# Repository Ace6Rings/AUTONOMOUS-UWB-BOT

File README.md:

# AUTONOMOUS-UWB-BOT
A ground robot with four UWB anchors to determine its location via TDoA or ToF.

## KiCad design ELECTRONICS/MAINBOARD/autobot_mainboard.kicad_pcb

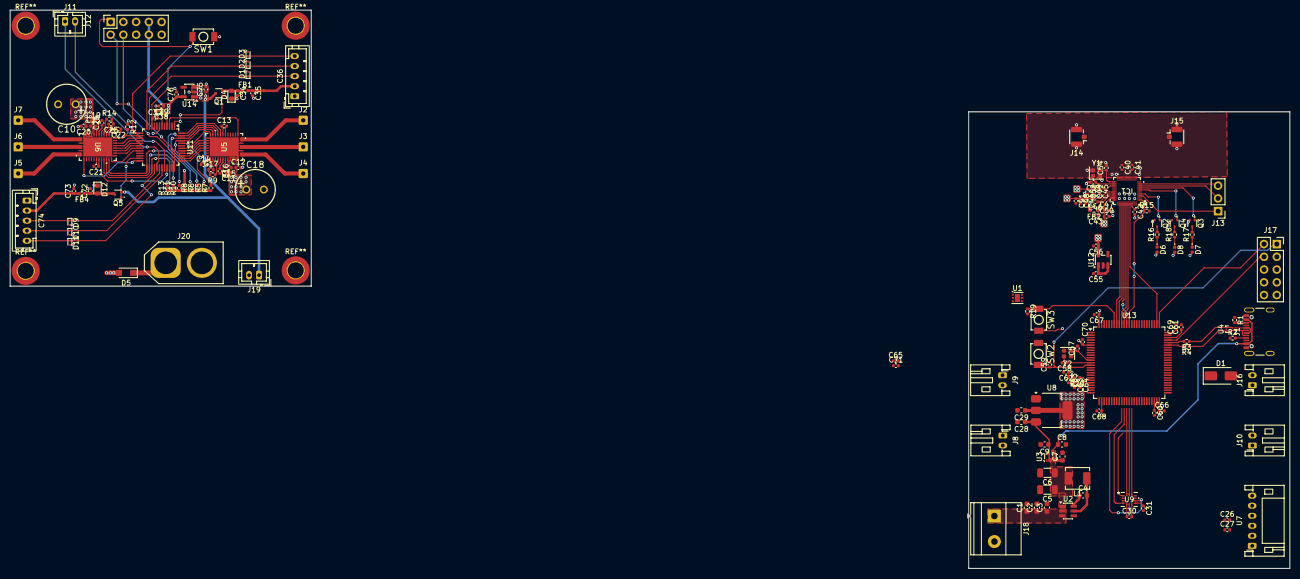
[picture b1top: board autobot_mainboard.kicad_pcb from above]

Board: 4 copper layers, 255.0 x 111.2 mm, 156 parts (0 on the bottom side), 122 nets.

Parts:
C1, C28, C29: 10u; C_0603_1608Metric
C2: 1u; C_0603_1608Metric
C3, C4, C7, C8: 100n; C_0603_1608Metric
C5, C6: 22u; C_1206_3216Metric
C9: 4u7; C_0603_1608Metric
C10, C18: 100u; CAP-TH_BD8.0-P3.50-D0.6-FD
C11, C12, C19, C20, C26, C30, C31, C37, C38, C42, C47, C48, C49, C59, C62, C64, C65, C66, C67, C68, C69, C70: 100n; C_0402_1005Metric
C13, C14, C15, C21, C22, C23, C55, C56, C63, C75, C76: 1u; C_0402_1005Metric
C16, C24: 47n; C_0402_1005Metric
C17, C25, C34, C35, C72, C73: C; C_0402_1005Metric
C27, C51, C52: 10u; C_0402_1005Metric
C36, C74: AMT-102-V; JST_PH_B5B-PH-K_1x05_P2.00mm_Vertical
C39, C71: 4u7; C_0402_1005Metric
C40, C41: 2p; C_0402_1005Metric
C43, C44, C45: 4.7n; C_0402_1005Metric
C46: 220n; C_0402_1005Metric
C50: 4.7u; C_0402_1005Metric
C53, C54, C57, C58: 12p; C_0402_1005Metric
C60, C61: 2.2u; C_0402_1005Metric
D1, D2, D3, D9, D10, D11: D_TVS; D_SOD-923
D1#2: SS24; D_SMA
D4, D12: D_TVS; D_0603_1608Metric
D5: PTVS17VZ1USK; Nexperia_CFP3_SOD-123W
D6, D7, D8: LED; LED_0402_1005Metric
FB1, FB3, FB4: FerriteBead_Small; R_0402_1005Metric
FB2: fb; R_0603_1608Metric
IC1: DW3210; qfn_DW3220_QOR-M
J1: USB_C_Receptacle_USB2.0_16P; USB_C_Receptacle_GCT_USB4105-xx-A_16P_TopMnt_Horizontal
J2, J3, J4, J5, J6, J7: Conn_01x01_Socket; SolderWire-0.25sqmm_1x01_D0.65mm_OD1.7mm
J8, J9, J10, J16: Conn_01x02_Pin; JST_PH_S2B-PH-K_1x02_P2.00mm_Horizontal
J11: Conn_01x02_Socket; JST_PH_B2B-PH-K_1x02_P2.00mm_Vertical
J12, J17: Conn_02x05_Odd_Even; PinSocket_2x05_P2.54mm_Vertical
J13: Conn_01x03_Pin; PinHeader_1x03_P2.54mm_Vertical
J14, J15: Conn_Coaxial; U.FL_Hirose_U.FL-R-SMT-1_Vertical
J18: Conn_01x02_Pin; TerminalBlock_Phoenix_MKDS-1,5-2-5.08_1x02_P5.08mm_Horizont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
J19: Conn_01x02_Pin; JST_PH_B2B-PH-K_1x02_P2.00mm_Vertical
J20: Conn_01x02_Pin; AMASS_XT60-F_1x02_P7.20mm_Vertical
L1: 4u7; L_Chilisin_BMRA00040415
Q1, Q2, Q3, Q4, Q5: DMG1012T; SOT-523
R1, R2: 5.1k; R_0402_1005Metric
R3, R4, R9, R14: 22; R_0402_1005Metric
R5, R6, R7, R8, R10, R11, R12, R13: 10K; R_0402_1005Metric
R15: 100K; R_0402_1005Metric
R16, R17, R18: R; R_0402_1005Metric
R19: 10k; R_0402_1005Metric
R20: 47; R_0402_1005Metric_Pad0.72x0.64mm_HandSolder
SW1: SW_Push; SW-SMD_L3.9-W3.0-P4.45
SW2: RESET; SW-SMD_L3.9-W3.0-P4.45
SW3: BOOT; SW-SMD_L3.9-W3.0-P4.45
U1: TVS1400DRV; WSON-6-1EP_2x2mm_P0.65mm_EP1x1.6mm
U2: AP63205WU; TSOT-23-6
U3: TPS2116DRL; SOT-583-8
U4: TPD2EUSB30A; Texas_DRT-3
U5, U6: VQFN40_RGF_TEX_mct8316
U7: VL53L1X; JST_PH_S6B-PH-K_1x06_P2.00mm_Horizontal
U8: NCP1117-3.3_SOT223; SOT-223-3_TabPin2
U9: BMI270; BMI270_BOS-M
U11: STM32G031C_4-6-8_Tx; LQFP-48_7x7mm_P0.5mm
U12, U14: LP5907MFX-3.3; SOT-23-5
U13: STM32H743VITx; LQFP-100_14x14mm_P0.5mm
Y1: TXC 8Y38472012; Crystal_SMD_2016-4Pin_2.0x1.6mm
Y2: 25mhz placeholder; Crystal_SMD_2016-4Pin_2.0x1.6mm

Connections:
+3V3: C26.1, C27.1, C29.1, C38.1, C39.1, C44.1, C45.1, C47.1, C48.1, C49.1, C50.1, C51.1, C52.1, C56.1, C62.1, C65.1, C66.1, C67.1, C68.1, C69.1, C70.1, C71.1, C76.1, D6.2 (A), D7.2 (A), D8.2 (A), FB2.2, FB3.1, IC1.23 (VDD2B), IC1.26 (VDD3), IC1.29 (VDD1), J12.7, J12.8, J17.7, J17.8, R5.1, R6.1, R7.1, R8.1, R10.1, R11.1, R12.1, R13.1, SW3.2, U7.1 (VIN), U8.2 (VO), U11.4 (VBAT), U11.6 (VDD), U12.5 (OUT), U13.6 (VBAT), U13.11 (VDD), U13.27 (VDD), U13.50 (VDD), U13.75 (VDD), U13.100 (VDD), U14.5 (OUT)
+5V: C9.1, C28.1, C30.1, C31.1, C34.1, C55.1, C72.1, C75.1, D4.2 (A2), D12.2 (A2), FB1.1, FB4.1, J19.1, Q1.2 (S), Q1.3 (D), Q5.2 (S), Q5.3 (D), U3.2 (VOUT), U3.7 (VOUT), U8.3 (VI), U9.5 (VDDIO), U9.8 (VDD), U12.1 (IN), U12.3 (EN), U14.1 (IN), U14.3 (EN)
+24V: C10.1, C11.1, C12.1, C15.1, C18.1, C19.1, C20.1, C23.1, D5.1 (K), J20.1, U5.9 (VM), U5.10 (VM), U5.11 (VM), U6.9 (VM), U6.10 (VM), U6.11 (VM)
/AMT102_L/AMT_A: C36.3 (A), D1.1 (A1), U11.11 (PA0)
/AMT102_L/AMT_B: C36.4 (B), D2.1 (A1), U11.12 (PA1)
/AMT102_L/AMT_GATE: Q1.1 (G), U11.1 (PC13)
/AMT102_L/AMT_X: C36.5 (X), D3.1 (A1), U11.13 (PA2)
/AMT102_R/AMT_A: C74.3 (A), D9.1 (A1), U11.30 (PC6)
/AMT102_R/AMT_B: C74.4 (B), D10.1 (A1), U11.31 (PC7)
/AMT102_R/AMT_GATE: Q5.1 (G), U11.23 (PB11)
/AMT102_R/AMT_X: C74.5 (X), D11.1 (A1), U11.28 (PA8)
/BMI270_L/BMI_CS: U9.12 (CSB), U13.41 (PE11)
/BMI270_L/BMI_MISO: U9.1 (SDO), U13.43 (PE13)
/BMI270_L/BMI_MOSI: U9.14 (SDX), U13.44 (PE14)
/BMI270_L/BMI_SCK: U9.13 (SCX), U13.42 (PE12)
/DW3220_T/CSN: IC1.37 (SPICSN), U13.77 (PA15)
/DW3220_T/DW_GPIO0: IC1.3 (GPIO0/_RXOKLED), J13.1
/DW3220_T/DW_GPIO4: IC1.8 (GPIO4/_EXTPA), J13.2
/DW3220_T/DW_GPIO7: IC1.9 (GPIO7/_SYNC), J13.3
/DW3220_T/DW_RF1: C40.1, J14.1 (In)
/DW3220_T/DW_RF2: C41.1, J15.1 (In)
/DW3220_T/IRQ: IC1.1 (IRQ/_GPIO8), R15.1, U13.88 (PD7)
/DW3220_T/MISO: IC1.36 (SPICDO_(SPIMISO)), U13.90 (PB4)
/DW3220_T/MOSI: IC1.35 (SPICDI_(SPIMOSI)), U13.91 (PB5)
/DW3220_T/RESET: IC1.33 (RSTN), U13.92 (PB6)
/DW3220_T/RXLED: IC1.6 (GPIO2_/_RXLED), Q4.1 (G)
/DW3220_T/RX_OK_LED: IC1.4 (GPIO1/_SFDLED), Q2.1 (G)
/DW3220_T/SPICLK: IC1.34 (SPICLK), U13.89 (PB3)
/DW3220_T/TXLED: IC1.7 (GPIO3_/_TXLED), Q3.1 (G)
/DW3220_T/WAKEUP: IC1.32 (WAKEUP), U13.93 (PB7)
/DW3220_T/XTI: C54.1, IC1.21 (XTI), Y1.3
/DW3220_T/XTO: C53.1, IC1.22 (XTO), Y1.1
/POWER_CONNECTOR/12V: C1.1, C2.1, C3.1, J18.1, U1.4 (IN), U1.5 (IN), U1.6 (IN), U2.2 (EN), U2.3 (IN)
/POWER_MAINBOARD/BUCK_5V: C5.1, C6.1, C7.1, L1.2, U2.1 (FB), U3.3 (VIN1), U3.4 (PR1), U3.5 (MODE)
/POWER_MAINBOARD/VBUS: C8.1, J1.A4 (VBUS), J1.A9 (VBUS), J1.B4 (VBUS), J1.B9 (VBUS), U3.6 (VIN2)
/STM32G0/BRAKE: U5.35 (BRAKE), U11.40 (PD2)
/STM32G0/BRAKE_R: U6.35 (BRAKE), U11.18 (PA7)
/STM32G0/DACOUT1: U5.37 (DACOUT1), U11.38 (PD0)
/STM32G0/DACOUT1_R: U6.37 (DACOUT1), U11.16 (PA5)
/STM32G0/DACOUT2: U5.38 (DACOUT2), U11.37 (PA15)
/STM32G0/DACOUT2_R: U6.38 (DACOUT2), U11.15 (PA4)
/STM32G0/DACOUT2/SOX: U5.36 (DACOUT2/SOX), U11.39 (PD1)
/STM32G0/DACOUT2/SOX_R: U6.36 (DACOUT2/SOX), U11.17 (PA6)
/STM32G0/DIR: U5.34 (DIR), U11.41 (PD3)
/STM32G0/DIR_R: U6.34 (DIR), U11.19 (PB0)
/STM32G0/DRVOFF: U5.21 (DRVOFF), U11.3 (PC15)
/STM32G0/DRVOFF_R: U6.21 (DRVOFF), U11.24 (PB12)
/STM32G0/EXT_WD: U5.32 (EXT_WD), U11.42 (PB3)
/STM32G0/EXT_WD_R: U6.32 (EXT_WD), U11.20 (PB1)
/STM32G0/FG: R8.2, U5.29 (FG), U11.47 (PB8)
/STM32G0/FG_R: R13.2, U6.29 (FG), U11.27 (PB15)
/STM32G0/PWM: U5.28 (SPEED/WAKE), U11.48 (PB9)
/STM32G0/PWM_R: U6.28 (SPEED/WAKE), U11.33 (PA9/PA11)
/STM32G0/SCL: R5.2, U5.31 (SCL), U11.45 (PB6)
/STM32G0/SCL_R: R10.2, U6.31 (SCL), U11.25 (PB13)
/STM32G0/SDA: R6.2, U5.30 (SDA), U11.46 (PB7)
/STM32G0/SDA_R: R11.2, U6.30 (SDA), U11.26 (PB14)
/STM32G0/SWCLK: J12.2, U11.36 (PA14)
/STM32G0/SWDIO: J12.4, U11.35 (PA13)
/STM32G0/USART_RX: J11.2, J16.1, U11.32 (NC/PA10), U13.53 (PB14)
/STM32G0/USART_TX: J11.1, J16.2, U11.29 (NC/PA9), U13.54 (PB15)
/STM32G0/nFAULT: R7.2, U5.40 (nFAULT), U11.44 (PB5)
/STM32G0/nFAULT_R: R12.2, U6.40 (nFAULT), U11.14 (PA3)
/STM32G0/nRESET: C37.1, J12.1, SW1.2, U11.10 (PF2)
/STM32H743/BOOT0: R19.1, SW3.1, U13.94 (BOOT0)
/STM32H743/D+: R3.2, U13.71 (PA12)
/STM32H743/D-: R4.2, U13.70 (PA11)
/STM32H743/NRST: C59.1, J17.1, SW2.2, U13.14 (NRST)
/STM32H743/PH0: C57.1, U13.12 (PH0), Y2.1
/STM32H743/PH1: C58.1, U13.13 (PH1), Y2.3
/STM32H743/SWCLK: J17.2, U13.76 (PA14)
/STM32H743/SWDIO: J17.4, U13.72 (PA13)
/STM32H743/VREF: R20.1, U13.20 (VREF+)
/USB/DATA +: J1.A6 (D+), J1.B6 (D+), R3.1, U4.2 (D-)
/USB/DATA -: J1.A7 (D-), J1.B7 (D-), R4.1, U4.1 (D+)
GNDREF: C1.2, C2.2, C3.2, C5.2, C6.2, C7.2, C8.2, C9.2, C10.2, C11.2, C12.2, C18.2, C19.2, C20.2, C26.2, C27.2, C28.2, C29.2, C30.2, C31.2, C34.2, C35.2, C36.1 (GND), C37.2, C38.2, C39.2, C42.2, C43.2, C44.2, C45.2, C46.2, C47.2, C48.2, C49.2, C50.2, C51.2, C52.2, C53.2, C54.2, C55.2, C56.2, C57.2, C58.2, C59.2, C60.2, C61.2, C62.2, C63.2, C64.2, C65.2, C66.2, C67.2, C68.2, C69.2, C70.2, C71.2, C72.2, C73.2, C74.1 (GND), C75.2, C76.2, D1.2 (A2), D2.2 (A2), D3.2 (A2), D4.1 (A1), D5.2 (A), D9.2 (A2), D10.2 (A2), D11.2 (A2), D12.1 (A1), IC1.2 (GPIO6_/_EXTRXE_/_SPIPHA), IC1.5 (GPIO5_/_EXTTXE_/_SPIPOL), IC1.10 (GND_1), IC1.11 (GND_2), IC1.12 (GND_3), IC1.14 (GND_4), IC1.15 (GND_5), IC1.16 (GND_6), IC1.17 (GND_7), IC1.19 (GND_8), IC1.20 (GND_9), IC1.24 (VSS2), IC1.25 (VSS3), IC1.30 (VSS1), IC1.39 (VSS), IC1.40 (VSS), J1.A1 (GND), J1.A12 (GND), J1.B1 (GND), J1.B12 (GND), J1.SH (SHIELD), J12.5, J12.6, J14.2 (Ext), J15.2 (Ext), J17.5, J17.6, J18.2, J19.2, J20.2, Q2.2 (S), Q3.2 (S), Q4.2 (S), R1.1, R2.1, R15.2, R19.2, SW1.1, SW2.1, U1.1 (GND), U1.2 (GND), U1.3 (GND), U1.7 (GND), U2.4 (GND), U3.1 (GND), U4.3 (GND), U5.12 (PGND), U5.15 (PGND), U5.18 (PGND), U5.33 (EXT_CLK), U5.41 (GNDPAD), U6.12 (PGND), U6.15 (PGND), U6.18 (PGND), U6.33 (EXT_CLK), U6.41 (GNDPAD), U7.2 (GND), U8.1 (GND), U9.6 (GNDIO), U9.7 (GND), U11.7 (VSS), U12.2 (GND), U13.10 (VSS), U13.19 (VSSA), U13.26 (VSS), U13.49 (VSS), U13.74 (VSS), U13.99 (VSS), U14.2 (GND), Y1.2 (G), Y1.4 (G), Y2.2 (G), Y2.4 (G)
unnamed: C35.1, C36.2 (VIN), FB1.2
unnamed: C60.1, U13.48 (VCAP)
unnamed: C61.1, U13.73 (VCAP)
unnamed: C73.1, C74.2 (VIN), FB4.2
unnamed: D6.1 (K), R16.1
unnamed: D7.1 (K), R17.1
unnamed: D8.1 (K), R18.1
unnamed: C40.2, IC1.18 (RF1)
unnamed: C41.2, IC1.13 (RF2)
unnamed: C43.1, FB2.1, IC1.28 (VDD2A)
unnamed: C42.1, IC1.38 (VIO_D)
unnamed: C46.1, IC1.27 (VTX_D)
unnamed: J1.A5 (CC1), R2.2
unnamed: J1.B5 (CC2), R1.2
unnamed: J2.1 (Pin_1_1), U5.19 (OUTC), U5.20 (OUTC)
unnamed: J3.1 (Pin_1_1), U5.16 (OUTB), U5.17 (OUTB)
unnamed: J4.1 (Pin_1_1), U5.13 (OUTA), U5.14 (OUTA)
unnamed: J5.1 (Pin_1_1), U6.19 (OUTC), U6.20 (OUTC)
unnamed: J6.1 (Pin_1_1), U6.16 (OUTB), U6.17 (OUTB)
unnamed: J7.1 (Pin_1_1), U6.13 (OUTA), U6.14 (OUTA)
unnamed: Q2.3 (D), R16.2
unnamed: Q3.3 (D), R17.2
unnamed: Q4.3 (D), R18.2
unnamed: C4.1, U2.6 (BST)
unnamed: C4.2, L1.1, U2.5 (SW)
unnamed: C13.2, U5.26 (AGND)
unnamed: C13.1, U5.27 (AVDD)
unnamed: C15.2, U5.8 (CP)
unnamed: C16.2, U5.7 (CPH)
unnamed: C16.1, U5.6 (CPL)
unnamed: C14.2, U5.2 (DGND)
unnamed: C14.1, U5.1 (DVDD)
unnamed: C17.1, R9.2, U5.3 (FB_BK)
unnamed: C17.2, U5.4 (GND_BK)
unnamed: R9.1, U5.5 (SW_BK)
unnamed: C21.2, U6.26 (AGND)
unnamed: C21.1, U6.27 (AVDD)
unnamed: C23.2, U6.8 (CP)
unnamed: C24.2, U6.7 (CPH)
unnamed: C24.1, U6.6 (CPL)
unnamed: C22.2, U6.2 (DGND)
unnamed: C22.1, U6.1 (DVDD)
unnamed: C25.1, R14.2, U6.3 (FB_BK)
unnamed: C25.2, U6.4 (GND_BK)
unnamed: R14.1, U6.5 (SW_BK)
unnamed: C63.1, C64.1, FB3.2, R20.2, U13.21 (VDDA)

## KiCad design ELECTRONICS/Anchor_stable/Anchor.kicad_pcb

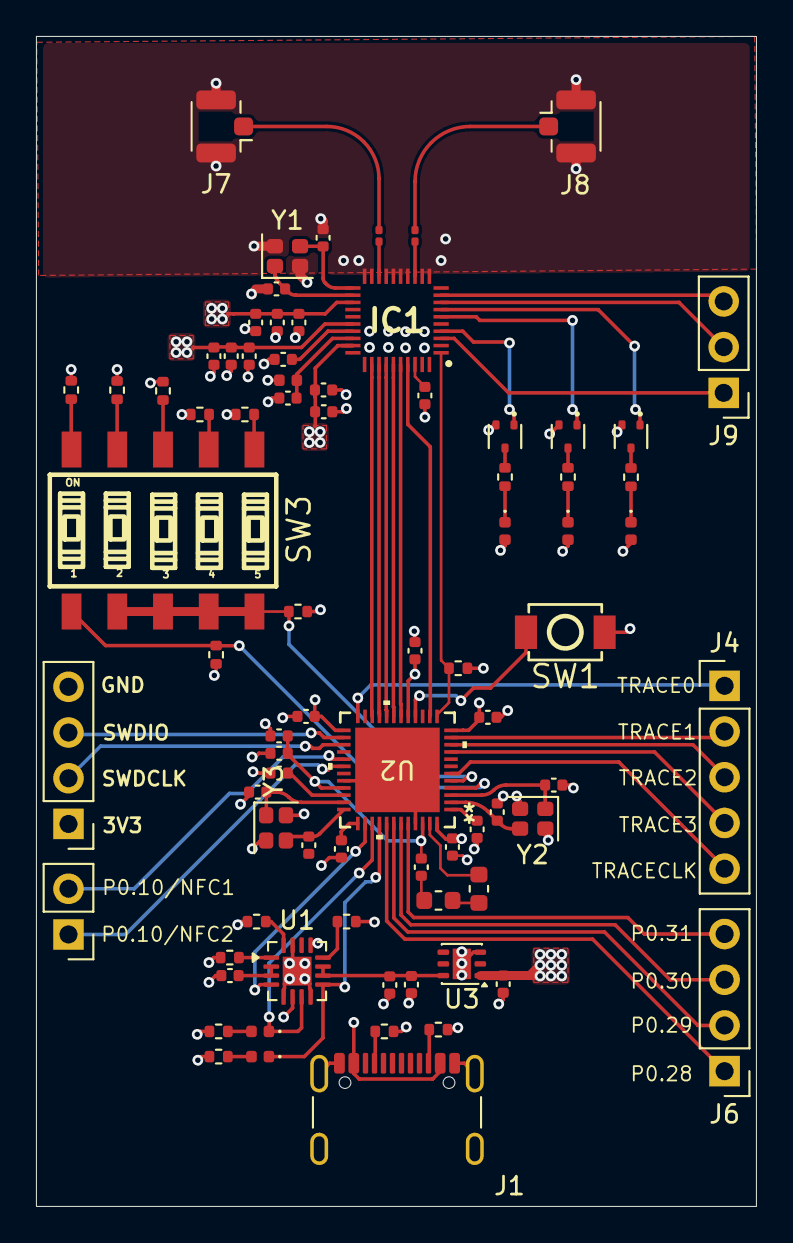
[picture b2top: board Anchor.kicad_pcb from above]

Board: 4 copper layers, 40.0 x 65.0 mm, 79 parts (0 on the bottom side), 74 nets.

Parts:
C1, C3, C17: 4.7u; C_0402_1005Metric
C2, C6, C9, C12, C19, C32, C33, C34, C35: 100n; C_0402_1005Metric
C4, C5, C8: 4.7n; C_0402_1005Metric
C7, C10: 10u; C_0402_1005Metric
C11: 220n; C_0402_1005Metric
C13, C31: 2p; C_0201_0603Metric
C15, C16, C23, C36: 1u; C_0402_1005Metric
C18: 47n; C_0402_1005Metric
C20: 100p; C_0402_1005Metric
C21: NC; C_0402_1005Metric
C25, C26, C27, C28, C29, C30: 12p; C_0402_1005Metric
D1, D2, D3, D4, D5: LED; LED_0402_1005Metric
FB1: fb; L_0402_1005Metric
IC1: DW3210; QFN40P500X500X80-40N-D
J1: USB_C_Receptacle_USB2.0_16P; USB_C_Receptacle_GCT_USB4105-xx-A_16P_TopMnt_Horizontal
J3, J6: Conn_01x04_Pin; PinHeader_1x04_P2.54mm_Vertical
J4: Conn_01x05_Pin; PinHeader_1x05_P2.54mm_Vertical
J5: Conn_01x02_Pin; PinHeader_1x02_P2.54mm_Vertical
J7, J8: Conn_Coaxial; U.FL_Hirose_U.FL-R-SMT-1_Vertical
J9: Conn_01x03_Pin; PinHeader_1x03_P2.54mm_Vertical
L3: 10u; L_0603_1608Metric
L4: 15u; L_0603_1608Metric
Q1, Q2, Q3: DMG1012T; SOT-523
R1, R2, R16: 5.1k; R_0402_1005Metric
R3, R4: 2.2K; R_0402_1005Metric
R5, R13, R17, R18, R19: 10k; R_0402_1005Metric
R6, R7, R9, R11, R12: R; R_0402_1005Metric
R10: 100K; R_0402_1005Metric
R14: 1k; R_0402_1005Metric
R15: 2.2k; R_0402_1005Metric
SW1: reset; SW-SMD_L3.9-W3.0-P4.45
SW3: SW_DIP_x05; SW-SMD_2.54-5P-TPGT
U1: BQ24075RGT; VQFN-16-1EP_3x3mm_P0.5mm_EP1.6x1.6mm
U2: NRF52840-QFAA-R7; QFN48_NRF52840-QFAA-R7_NOR
U3: AP7370-33FDC; DFN-6-1EP_2x2mm_P0.65mm_EP1.01x1.7mm
Y1: TXC 8Y38472012; Crystal_SMD_2016-4Pin_2.0x1.6mm
Y2: ECS-320-8-37B-CKY-TR; Crystal_SMD_2016-4Pin_2.0x1.6mm
Y3: ECS-.327-6-1210B-N-TR; Crystal_SMD_2016-4Pin_2.0x1.6mm

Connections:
+3V3: C2.1, C3.1, C5.1, C6.1, C7.1, C8.1, C9.1, C10.1, C16.1, C32.1, C33.1, C34.1, C35.1, C36.1, D3.2 (A), D4.2 (A), D5.2 (A), FB1.2, IC1.23 (VDD2B), IC1.26 (VDD3), IC1.29 (VDD1), J3.1, R6.2, R7.2, R13.2, R14.2, R15.2, R16.2, R17.2, U2.12 (VDD), U2.17 (VDD), U2.25 (VDD), U2.37 (VDD), U2.48 (VDD), U3.1 (VO)
/BAT+: C1.1, U1.2 (BAT), U1.3 (BAT)
/BQ_OUT: C15.1, C17.1, U1.10 (OUT), U1.11 (OUT), U3.6 (VI)
/CE: U1.4 (~CE), U2.38 (P1.15)
/CHG: D2.1 (K), U1.9 (~CHG), U2.40 (P0.02/AIN0)
/DW_GPIO0: IC1.3 (GPIO0/_RXOKLED), J9.1
/DW_GPIO4: IC1.8 (GPIO4/_EXTPA), J9.2
/DW_GPIO7: IC1.9 (GPIO7/_SYNC), J9.3
/DW_RF1: C13.1, J7.1 (In)
/DW_RF2: C31.1, J8.1 (In)
/DW_RST: IC1.33 (RSTN), U2.21 (P0.22/QSPI)
/ID_SEL: R18.2, SW3.2, SW3.3, SW3.4, SW3.5, U2.5 (P0.05/AIN3)
/IRQ: IC1.1 (IRQ/_GPIO8), R10.1, U2.13 (P0.13)
/MODE_SEL: R19.2, SW3.1, U2.4 (P0.04/AIN2)
/P0.09/NFC1: J5.2, U2.29 (P0.09/NFC1)
/P0.10/NFC2: J5.1, U2.30 (P0.10/NFC2)
/P0.28/AIN4: J6.1, U2.41 (P0.28/AIN4)
/P0.29/AIN5: J6.2, U2.42 (P0.29/AIN5)
/P0.30/AIN6: J6.3, U2.43 (P0.30/AIN6)
/P0.31/AIN7: J6.4, U2.44 (P0.31/AIN7)
/PGOOD: D1.1 (K), U1.7 (~PGOOD), U2.39 (P0.03/AIN1)
/RXLED: IC1.6 (GPIO2_/_RXLED), Q2.1 (G)
/RX_OK_LED: IC1.4 (GPIO1/_SFDLED), Q1.1 (G)
/SPICLK: IC1.34 (SPICLK), U2.18 (P0.19/QSPI/SCK)
/SPICSN: IC1.37 (SPICSN), U2.14 (P0.14)
/SPIMISO: IC1.36 (SPICDO_(SPIMISO)), U2.20 (P0.21/QSPI)
/SPIMOSI: IC1.35 (SPICDI_(SPIMOSI)), U2.19 (P0.20)
/SWDCLK: J3.2, U2.27 (SWDCLK)
/SWDIO: J3.3, U2.26 (SWDIO)
/TRACECLK: J4.5, U2.6 (P0.07/TRACECLK)
/TRACEDATA0: J4.1, U2.24 (P1.00/TRACEDATA0/QSPI)
/TRACEDATA1: J4.2, U2.11 (P0.11/TRACEDATA1)
/TRACEDATA2: J4.3, U2.10 (P0.11/TRACEDATA2)
/TRACEDATA3: J4.4, U2.9 (P1.09/TRACEDATA3)
/TXLED: IC1.7 (GPIO3_/_TXLED), Q3.1 (G)
/WAKEUP: IC1.32 (WAKEUP), U2.22 (P0.23/QSPI)
/XC1: C29.1, U2.35 (XC1), Y3.1
/XC2: C30.1, U2.36 (XC2), Y3.3
/XL1: C27.1, U2.3 (P0.01/XL2), Y2.1
/XL2: C28.1, U2.2 (P0.00/XL1), Y2.3
/XTI: C26.1, IC1.21 (XTI), Y1.3
/XTO: C25.1, IC1.22 (XTO), Y1.1
GNDREF: C1.2, C2.2, C3.2, C4.2, C5.2, C6.2, C7.2, C8.2, C9.2, C10.2, C11.2, C12.2, C15.2, C16.2, C17.2, C18.2, C19.2, C20.2, C21.2, C25.2, C26.2, C27.2, C28.2, C29.2, C30.2, C32.2, C33.2, C34.2, C35.2, C36.2, IC1.2 (GPIO6_/_EXTRXE_/_SPIPHA), IC1.5 (GPIO5_/_EXTTXE_/_SPIPOL), IC1.10 (GND_1), IC1.11 (GND_2), IC1.12 (GND_3), IC1.14 (GND_4), IC1.15 (GND_5), IC1.16 (GND_6), IC1.17 (GND_7), IC1.19 (GND_8), IC1.20 (GND_9), IC1.24 (VSS2), IC1.25 (VSS3), IC1.30 (VSS1), IC1.39 (VSS), IC1.40 (VSS), J1.A1 (GND), J1.A12 (GND), J1.B1 (GND), J1.B12 (GND), J1.SH (SHIELD), J3.4, J7.2 (Ext), J8.2 (Ext), Q1.2 (S), Q2.2 (S), Q3.2 (S), R1.2, R2.2, R3.2, R4.2, R5.2, R10.2, R18.1, R19.1, SW1.1, U1.5 (EN2), U1.8 (VSS), U1.15 (SYSOFF), U1.17 (VSS), U2.32 (VSS_PA), U2.45 (VSS), U2.49 (VSS), U3.3 (GND), U3.7 (GND), Y1.2 (G), Y1.4 (G), Y2.2 (G), Y2.4 (G), Y3.2 (G), Y3.4 (G)
unnamed: C23.1, L4.1
unnamed: D1.2 (A), R6.1
unnamed: D2.2 (A), R7.1
unnamed: D3.1 (K), R9.1
unnamed: D4.1 (K), R11.1
unnamed: D5.1 (K), R12.1
unnamed: C13.2, IC1.18 (RF1)
unnamed: C31.2, IC1.13 (RF2)
unnamed: C4.1, FB1.1, IC1.28 (VDD2A)
unnamed: C12.1, IC1.38 (VIO_D)
unnamed: C11.1, IC1.27 (VTX_D)
unnamed: J1.A5 (CC1), R2.1
unnamed: J1.B5 (CC2), R1.1
unnamed: L3.1, L4.2
unnamed: Q1.3 (D), R9.2
unnamed: Q2.3 (D), R11.2
unnamed: Q3.3 (D), R12.2
unnamed: R13.1, SW3.10
unnamed: R14.1, SW3.9
unnamed: R15.1, SW3.8
unnamed: R16.1, SW3.7
unnamed: R17.1, SW3.6
unnamed: R3.1, U1.12 (ILIM)
unnamed: R4.1, U1.16 (ISET)
unnamed: R5.1, U1.1 (TS)
unnamed: L3.2, U2.47 (DCC)
unnamed: C19.1, U2.1 (DEC1)
unnamed: C20.1, U2.34 (DEC3)
unnamed: C18.1, C21.1, C23.2, U2.33 (DEC6), U2.46 (DEC4)
unnamed: SW1.2, U2.16 (P0.18/RESET/QSPI/CSN)
VBUS: J1.A4 (VBUS), J1.A9 (VBUS), J1.B4 (VBUS), J1.B9 (VBUS), U1.6 (EN1), U1.13 (IN)

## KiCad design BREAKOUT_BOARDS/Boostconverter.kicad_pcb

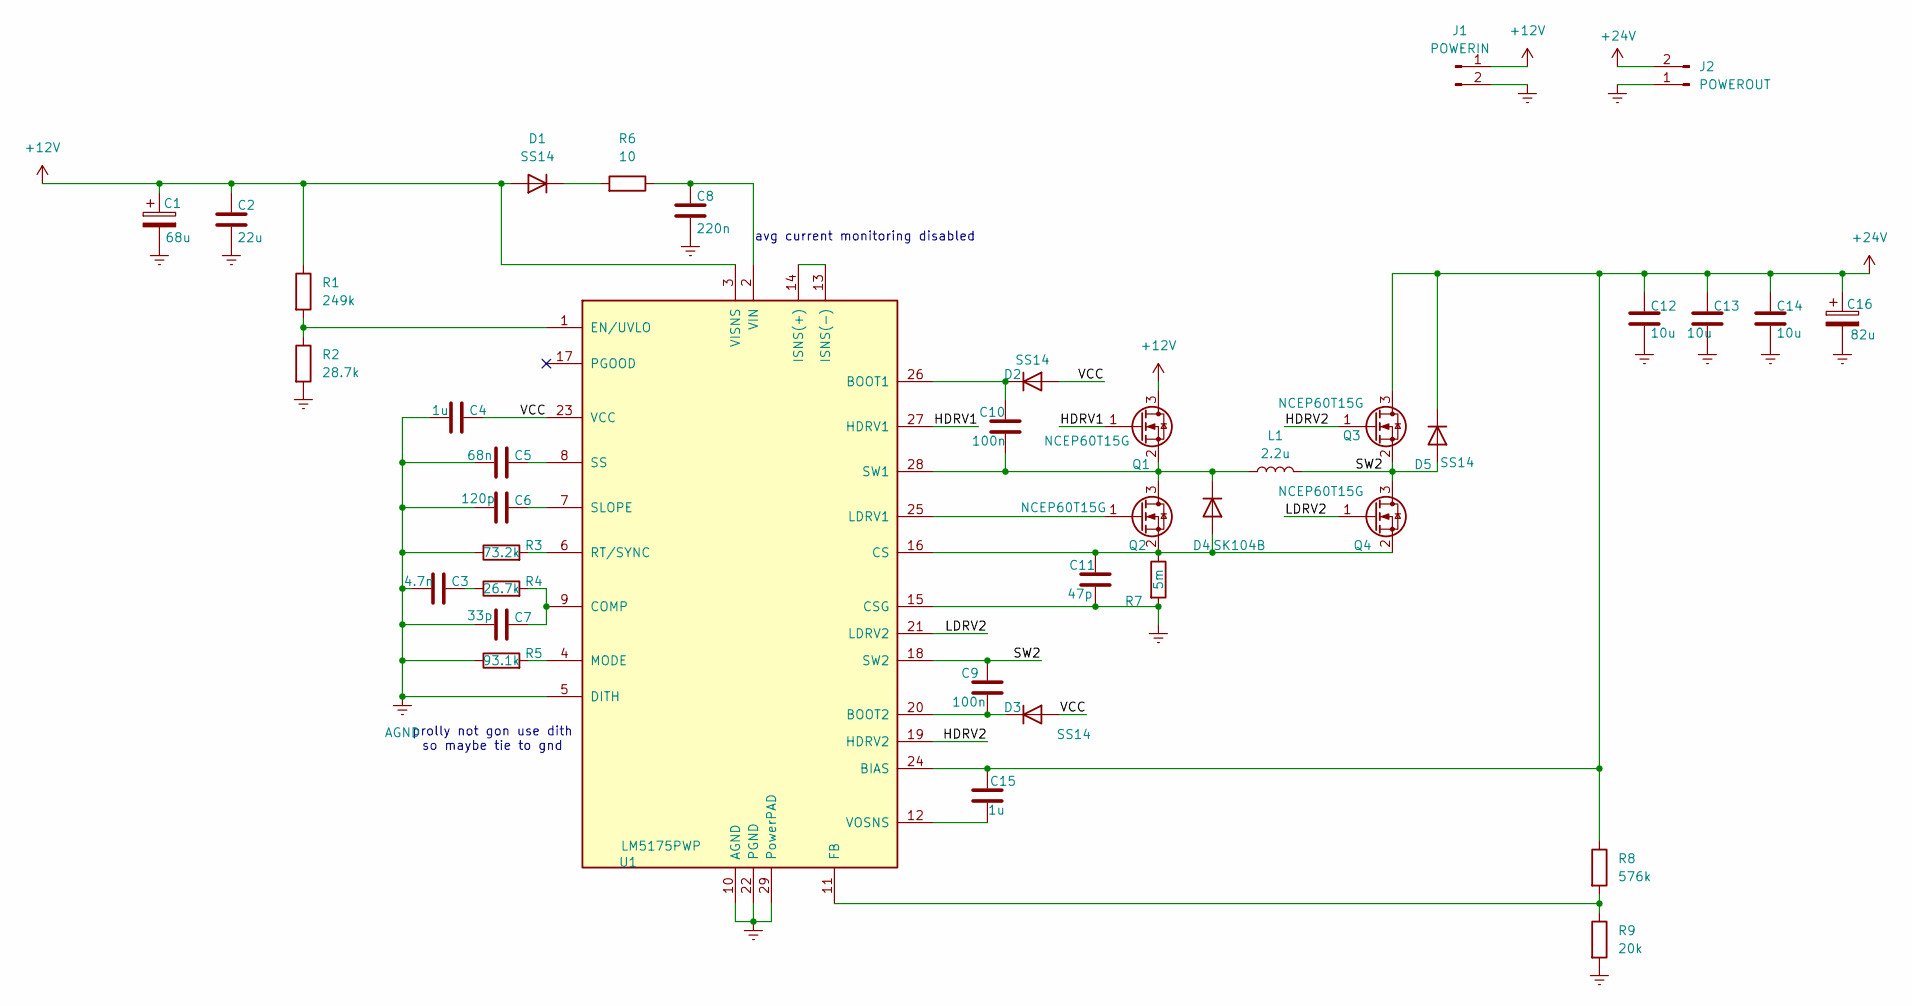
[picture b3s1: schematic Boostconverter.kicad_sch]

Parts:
C1: 68u; PCAP_SVP_F12_PAN-M
C2: 22u; C_1210_3225Metric
C3: 4.7n; C_0603_1608Metric
C4, C15: 1u; C_0603_1608Metric
C5: 68n; C_0603_1608Metric
C6: 120p; C_0603_1608Metric
C7: 33p; C_0402_1005Metric
C8: 220n; C_0603_1608Metric
C9, C10: 100n; C_0603_1608Metric
C11: 47p; C_0402_1005Metric
C12, C13, C14: 10u; C_1210_3225Metric
C16: 82u; CAP_35SVPF82M
D1, D2, D3, D5: SS14; D_SMA
D4: SK104B; D_SMB
J1: POWERIN; TerminalBlock_Phoenix_MKDS-1,5-2-5.08_1x02_P5.08mm_Horizont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
J2: POWEROUT; TerminalBlock_Phoenix_MKDS-1,5-2-5.08_1x02_P5.08mm_Horizont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
L1: 2.2u; L_Coilcraft_XAL1010-XXX
Q1, Q2, Q3, Q4: NCEP60T15G; AO_DFN-8-1EP_5.55x5.2mm_P1.27mm_EP4.12x4.6mm
R1: 249k; R_0603_1608Metric
R2: 28.7k; R_0603_1608Metric
R3: 73.2k; R_0603_1608Metric
R4: 26.7k; R_0603_1608Metric
R5: 93.1k; R_0603_1608Metric
R6: 10; R_0603_1608Metric
R7: 5m; R_1206_3216Metric
R8: 576k; R_0603_1608Metric
R9: 20k; R_0603_1608Metric
U1: LM5175PWP; VQFN-28-1EP_4x5mm_P0.5mm_EP2.55x3.55mm

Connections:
+12V: C1.1, C2.1, D1.2 (A), J1.1, Q1.3 (D), R1.1, U1.3 (VISNS)
+24V: C12.1, C13.1, C14.1, C15.1, C16.1, D5.1 (K), J2.2, Q3.3 (D), R8.1, U1.24 (BIAS)
/HDRV1: Q1.1 (G), U1.27 (HDRV1)
/HDRV2: Q3.1 (G), U1.19 (HDRV2)
/LDRV2: Q4.1 (G), U1.21 (LDRV2)
/SW2: C9.1, D5.2 (A), L1.2, Q3.2 (S), Q4.3 (D), U1.18 (SW2)
/VCC: C4.2, D2.2 (A), D3.2 (A), U1.23 (VCC)
AGND: C3.1, C4.1, C5.1, C6.1, C7.1, R3.1, R5.1, U1.5 (DITH)
GNDREF: C1.2, C2.2, C8.2, C11.2, C12.2, C13.2, C14.2, C16.2, J1.2, J2.1, R2.2, R7.2, R9.2, U1.10 (AGND), U1.15 (CSG), U1.22 (PGND), U1.29 (PowerPAD)
unnamed: C3.2, R4.1
unnamed: D1.1 (K), R6.2
unnamed: C10.1, D2.1 (K), U1.26 (BOOT1)
unnamed: C9.2, D3.1 (K), U1.20 (BOOT2)
unnamed: C11.1, D4.2 (A), Q2.2 (S), Q4.2 (S), R7.1, U1.16 (CS)
unnamed: C10.2, D4.1 (K), L1.1, Q1.2 (S), Q2.3 (D), U1.28 (SW1)
unnamed: Q2.1 (G), U1.25 (LDRV1)
unnamed: C7.2, R4.2, U1.9 (COMP)
unnamed: R1.2, R2.1, U1.1 (EN/UVLO)
unnamed: R8.2, R9.1, U1.11 (FB)
unnamed: U1.13 (ISNS(-)), U1.14 (ISNS(+))
unnamed: R5.2, U1.4 (MODE)
unnamed: R3.2, U1.6 (RT/SYNC)
unnamed: C6.2, U1.7 (SLOPE)
unnamed: C5.2, U1.8 (SS)
unnamed: C8.1, R6.1, U1.2 (VIN)
unnamed: C15.2, U1.12 (VOSNS)

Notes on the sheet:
prolly not gon use dith so maybe tie to gnd
avg current monitoring disabled

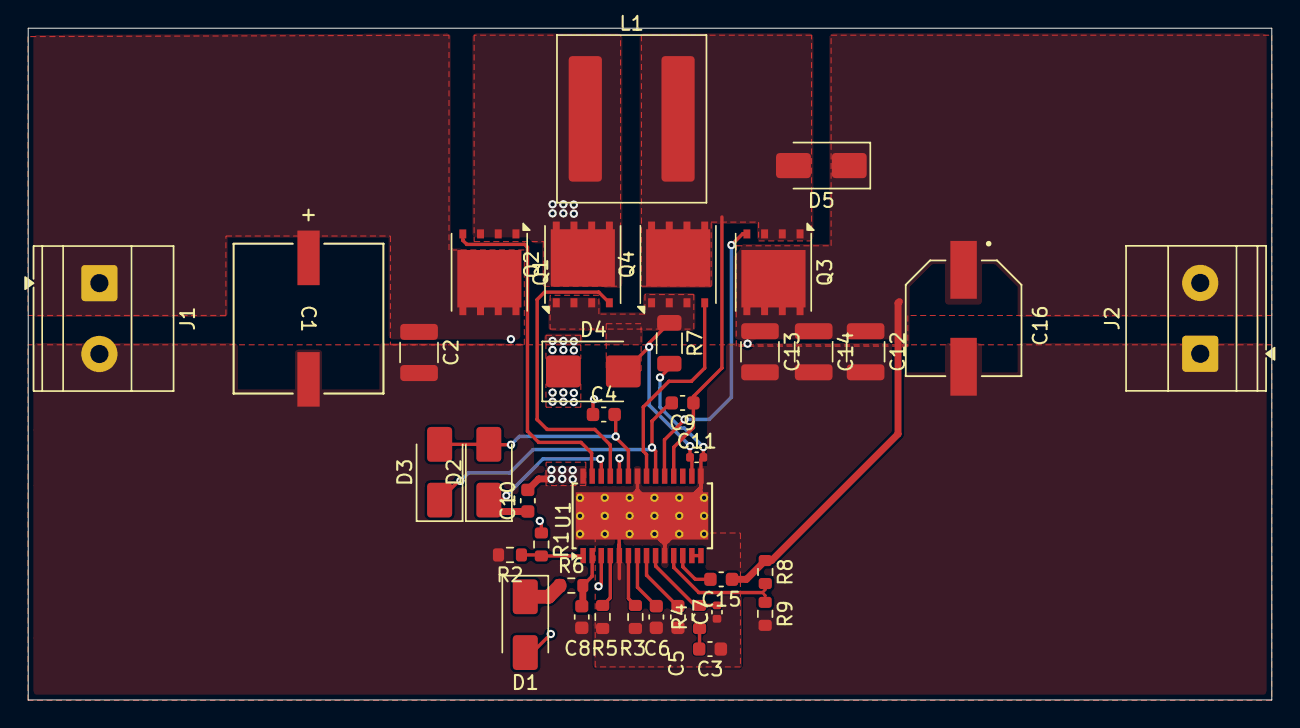
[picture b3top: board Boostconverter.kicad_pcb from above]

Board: 4 copper layers, 89.2 x 48.2 mm, 38 parts (0 on the bottom side), 26 nets.
